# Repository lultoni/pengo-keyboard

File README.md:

# pengo-keyboard
This is a collection of files that I made and used in the creation process of my personalized ergonomic split keyboard.

If there are any questions about this repository you should read my paper about the project, as I cover everything about the project in there in detail.
The paper can be found in the 'additional-files' folder.

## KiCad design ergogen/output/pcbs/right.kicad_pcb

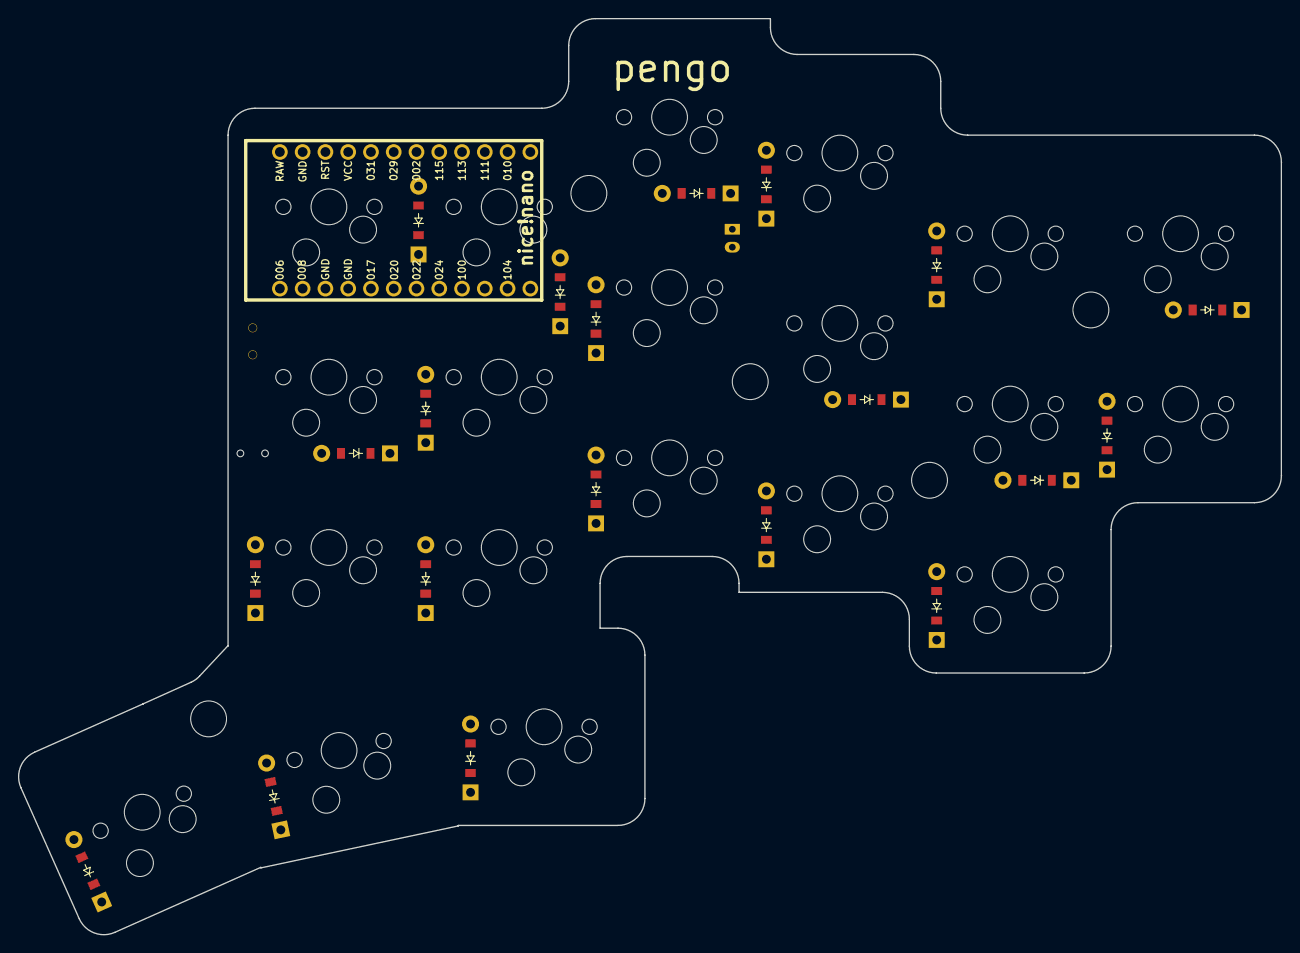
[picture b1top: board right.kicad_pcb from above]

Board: 2 copper layers, 140.9 x 102.2 mm, 44 parts (0 on the bottom side), 34 nets, no tracks yet.

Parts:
B1: Panasonic_EVQPUL_EVQPUC
D1, D2, D3, D4, D5, D6, D7, D8, D9, D10, D11, D12, D13, D14, D15, D16, D17, D18, D19, D20: ComboDiode
JST1: JST_PH_S2B-PH-K_02x2.00mm_Angled
MCU1: nice_nano
S1, S2, S3, S4, S5, S6, S7, S8, S9, S10, S11, S12, S13, S14, S15, S16, S17, S18, S19, S20: MX
T1: SPDT_C128955

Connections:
GND: B1.1, JST1.2, MCU1.3, MCU1.4, MCU1.23
P002: D2.1, D4.1, D6.1, D8.1, D10.1, MCU1.18
P011: MCU1.10, S12.1, S13.1, S14.1, S19.1
P017: MCU1.5, S15.1, S16.1, S17.1, S20.1
P020: MCU1.6, S1.1, S2.1
P022: MCU1.7, S3.1, S4.1, S5.1
P024: MCU1.8, S6.1, S7.1, S8.1
P029: D1.1, D7.1, D9.1, D15.1, D18.1, D19.1, MCU1.19
P031: D3.1, D5.1, D14.1, D16.1, D17.1, D20.1, MCU1.20
P100: MCU1.9, S9.1, S10.1, S11.1, S18.1
P115: D11.1, D12.1, D13.1, MCU1.17
RAW: MCU1.24, T1.2
RST: B1.2, MCU1.22
mirror_far_thumb: D13.2, S20.2
mirror_home_thumb: D12.2, S19.2
mirror_index_bottom: D8.2, S12.2
mirror_index_home: D9.2, S13.2
mirror_index_top: D16.2, S14.2
mirror_inner_bottom: D10.2, S15.2
mirror_inner_home: D15.2, S16.2
mirror_inner_top: D14.2, S17.2
mirror_middle_bottom: D6.2, S9.2
mirror_middle_home: D7.2, S10.2
mirror_middle_top: D17.2, S11.2
mirror_near_thumb: D11.2, S18.2
mirror_outer_home: D1.2, S1.2
mirror_outer_top: D20.2, S2.2
mirror_pinky_bottom: D2.2, S3.2
mirror_pinky_home: D19.2, S4.2
mirror_pinky_top: D3.2, S5.2
mirror_ring_bottom: D4.2, S6.2
mirror_ring_home: D18.2, S7.2
mirror_ring_top: D5.2, S8.2
pos: JST1.1, T1.1

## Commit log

2024-09-24 Create LICENSE
2024-09-24 Added Python Files
2024-09-24 config presave
2024-09-24 config errorsave
2024-09-24 wrong component positions
2024-09-24 mounting holes, nice nano, reset, power - correct pos
2024-09-25 pre footnote save
2024-09-25 Only few diodes left
2024-09-25 Pre-Routing Commit
2024-09-25 file organization
2024-09-25 configured key nets correct
2024-09-25 Too many unrouted
2024-09-25 done with the pcbs finally
2024-09-25 created gerber files
2024-09-30 after reset case and zmk start
2024-10-01 firmware is done
2024-10-01 start case design blender
2024-10-02 case_pt_02 blender
2024-10-06 autodesk depression quicksave
2024-10-07 start docs latex
2024-10-07 A lot of work left on latex
2024-10-15 General Maintenace
2024-10-16 Corrected the size of the plate_prototype
2024-10-16 First real done case prototype
2024-10-28 finished case prototype v2
2024-10-29 prototype v3 done
